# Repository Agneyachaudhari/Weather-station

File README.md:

# Weather-station
Full fleged weather station powered by solar

__Status__
This is a work in progress. So far the project uses the following Electronics: \
ESP-32 WROOM-32e               x1 \
AMS1117-3.3		       x1 \
10k 1/4 Watt Resiters          x10\
(minimum i could get)\
DHT11 module                   x1 \
BH1750 GY-302 module           x1 \
PMS5303                        x1 \
IRLZ44N MOSFET                 x1 \
18650 double battery holder    x1 \
Samsung INR18650-25R 2500Mah   x1 \
Solar power manager 5V         x1 \
6V 3W solar panel              x2 \
IP65 Project box	       x1 \
PCB                            x5 \

I have not yet procured these and i have not made code for them. I have designed the PCBs.

__Images of pcb in KiCAD__

Schematic :

PCB :

3D Viewer :

Front :

Back :

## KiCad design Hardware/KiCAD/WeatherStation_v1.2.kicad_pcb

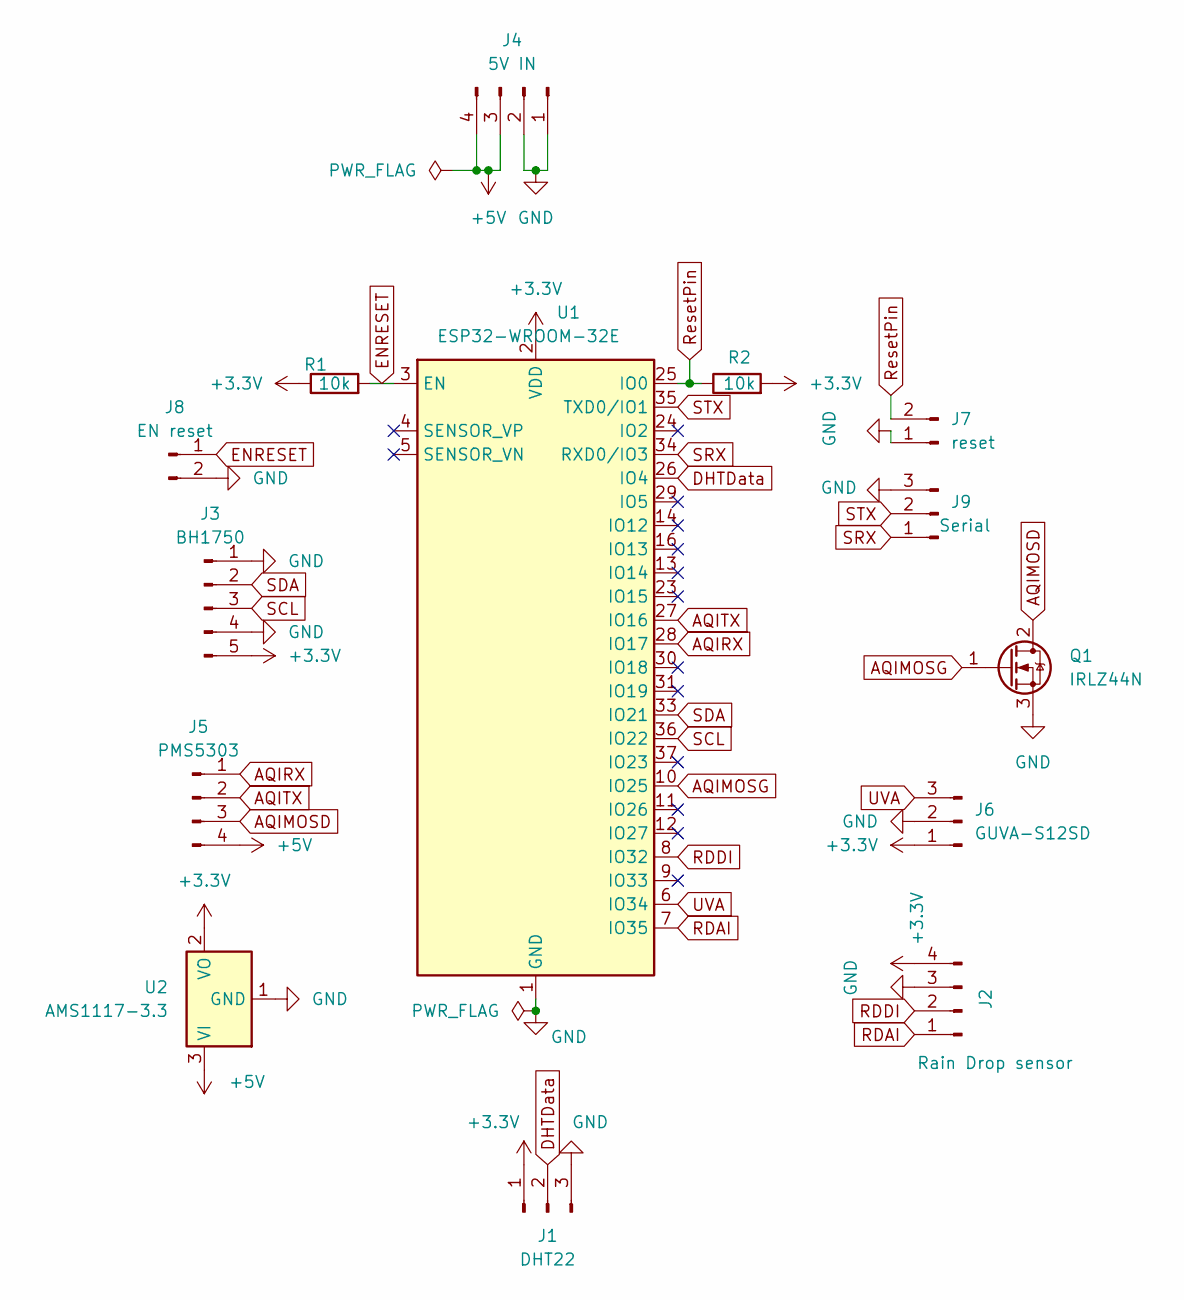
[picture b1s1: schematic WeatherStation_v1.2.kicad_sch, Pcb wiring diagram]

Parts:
J1: DHT22; PinHeader_1x03_P2.54mm_Vertical
J2: Rain Drop sensor; PinHeader_1x04_P2.54mm_Vertical
J3: BH1750; PinHeader_1x05_P2.54mm_Vertical
J4: 5V IN; PinHeader_1x04_P2.54mm_Vertical
J5: PMS5303; PinHeader_1x04_P2.54mm_Vertical
J6: GUVA-S12SD; PinHeader_1x03_P2.54mm_Vertical
J7: reset; SolderJumper-2_P1.3mm_Open_TrianglePad1.0x1.5mm
J8: EN reset; SolderJumper-2_P1.3mm_Open_TrianglePad1.0x1.5mm
J9: Serial; PinHeader_1x03_P2.54mm_Vertical
Q1: IRLZ44N; TO-220-3_Vertical
R1, R2: 10k; R_Axial_DIN0207_L6.3mm_D2.5mm_P7.62mm_Horizontal
U1: ESP32-WROOM-32E; ESP32-WROOM-32D
U2: AMS1117-3.3; SOT-223-3_TabPin2

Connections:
+3.3V: J1.1, J2.4, J3.5, J6.1, R1.1, R2.2, U1.2 (VDD), U2.2 (VO)
+5V: J4.3, J4.4, J5.4, U2.3 (VI)
AQIMOSD: J5.3, Q1.2 (D)
AQIMOSG: Q1.1 (G), U1.10 (IO25)
AQIRX: J5.1, U1.28 (IO17)
AQITX: J5.2, U1.27 (IO16)
DHTData: J1.2, U1.26 (IO4)
ENRESET: J8.1, R1.2, U1.3 (EN)
GND: J1.3, J2.3, J3.1, J3.4, J4.1, J4.2, J6.2, J7.1, J8.2, J9.3, Q1.3 (S), U1.1 (GND), U1.15 (GND), U1.38 (GND), U1.39 (GND), U2.1 (GND)
RDAI: J2.1, U1.7 (IO35)
RDDI: J2.2, U1.8 (IO32)
ResetPin: J7.2, R2.1, U1.25 (IO0)
SCL: J3.3, U1.36 (IO22)
SDA: J3.2, U1.33 (IO21)
SRX: J9.1, U1.34 (RXD0/IO3)
STX: J9.2, U1.35 (TXD0/IO1)
UVA: J6.3, U1.6 (IO34)

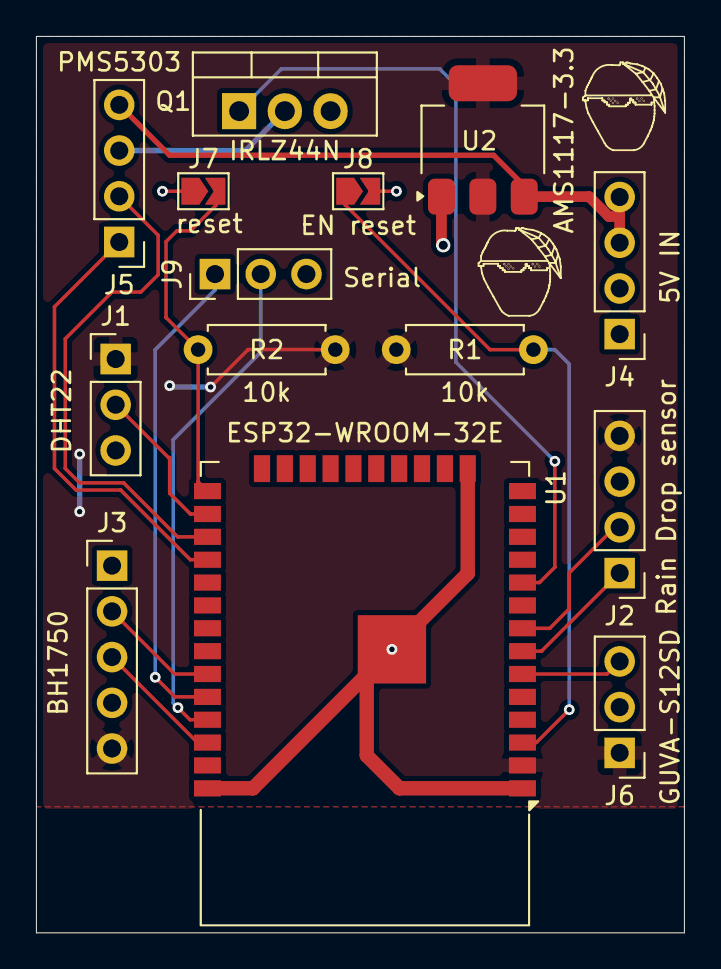
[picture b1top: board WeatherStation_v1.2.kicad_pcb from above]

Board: 2 copper layers, 36.0 x 49.8 mm, 15 parts (1 on the bottom side), 17 nets.

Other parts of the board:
mango: Untitled; 25mm

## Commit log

2026-05-01 Update README with project status and components
    Added project status and list of electronics used.
2026-05-01 Revise README with project status and components list
    Updated project status and added details about components and PCB design.
2026-05-13 Add stuff to repo
2026-05-21 Update README
    Added images of PCB schematics and 3D views to README.
2026-06-02 Added a BOM.csv and updated Gerber filenames and make KiCAD files link correctly
